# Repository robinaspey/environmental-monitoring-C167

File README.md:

# C167 environmental-monitoring source code
Legacy code for Siemens C167 microcontroller board which was for the EU Transport futures project. The Compiler used was KEIL Microvision 2. Assembler and Ansi C as well as binary files from the board OEM are included although the ASM and C driver and main program files were for the project. The additional hardware for the board was a custom photodetector board which had gain increments of x10, x100 and x1000 under control of the C167 dependent on the signal level

This code reads the ADC values for R,G,B channels from a photovolaic spectrometer which used the Mazet 3 channel photo diode with an OPA111 preamplifier from Burr Brown. The probe was used in the exhaust of a bus, and was also tested with various smoke sources
to allow detection of particulates and particulat bursts during vehicle operation.

This is legacy source code from 2001, so another of my old embedded projects

The files are all Ansi C and include:

1. Project main file: mtf0.c, mtf1.c, mtf2.c, mtf3.c, mtf4.c (revisions not under VCS)
2. Flash memory file system file (ff_flash.c)
3. Drivers for the main program  

Interfacing to the microcontroller is via a monitor program which is accessed by the serial
terminal and pressing <ESC> while the microcontroller reboots.

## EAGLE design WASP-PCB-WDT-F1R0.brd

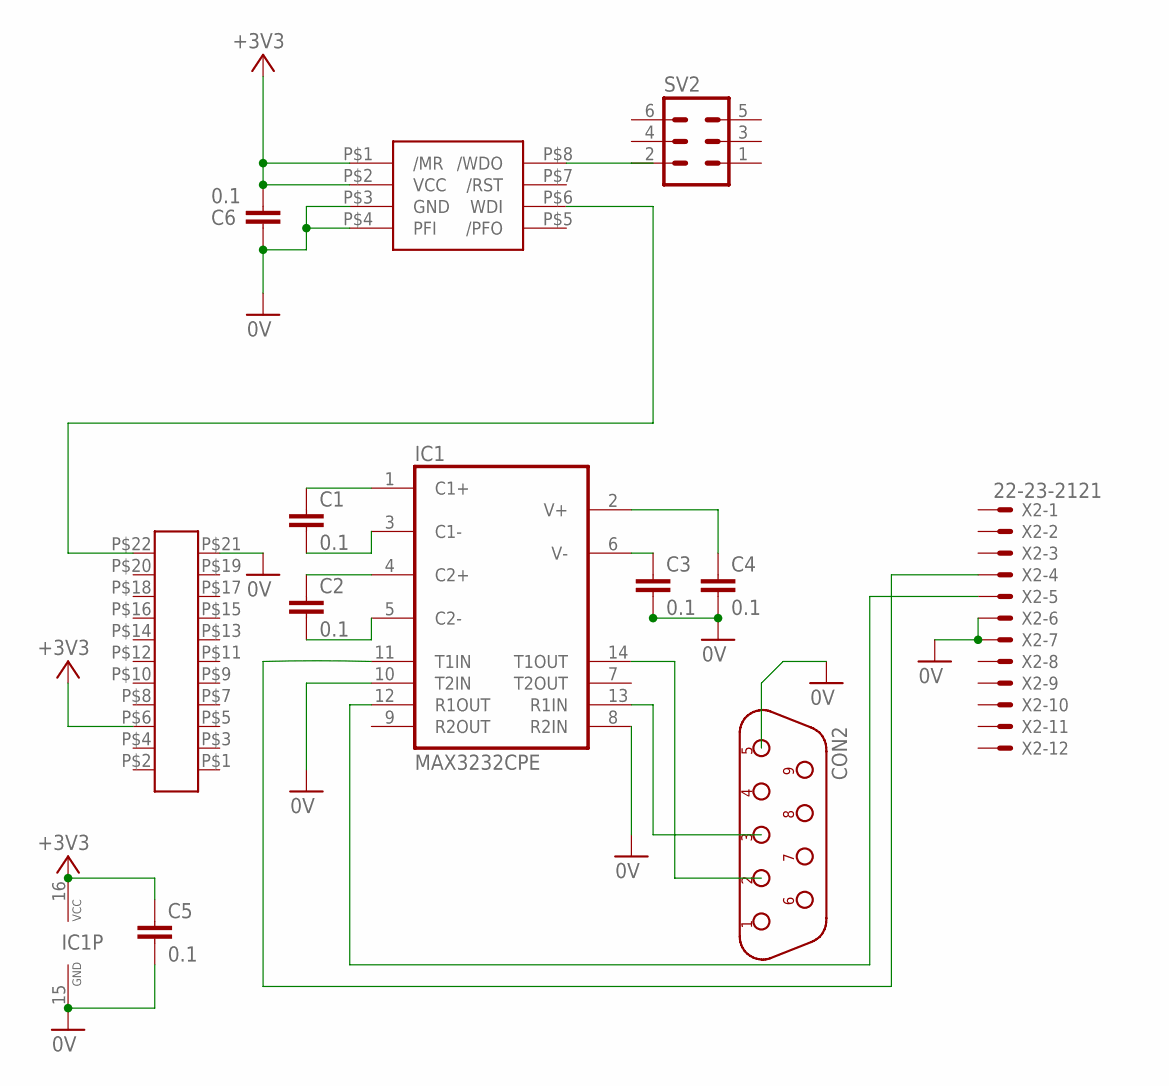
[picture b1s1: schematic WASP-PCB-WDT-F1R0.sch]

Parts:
C1, C2, C3, C4, C5, C6: 0.1; C5B2.5
CON2: CONNECT_DB9F/90; CONNECT_D-09F/90
IC1: MAX3232CPE; DIL16
SV2: CON-ML_ML6
U$2: ML22PML22P-PKG; CON-ML-22P
U$3: ADM706P
X2: 22-23-2121

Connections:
0V: C3.2, C4.2, C5.2, C6.2, CON2.5, IC1.8 (R2IN), IC1.10 (T2IN), IC1.15 (GND), U$2.P$21 (21), U$3.P$3 (GND), U$3.P$4 (PFI), X2.6, X2.7
14: U$2.P$14 (14)
+3V3: C5.1, C6.1, IC1.16 (VCC), U$2.P$6 (6), U$3.P$1 (/MR), U$3.P$2 (VCC)
unnamed: U$2.P$22 (22), U$3.P$6 (WDI)
unnamed: C1.1, IC1.1 (C1+)
unnamed: C1.2, IC1.3 (C1-)
unnamed: C2.1, IC1.4 (C2+)
unnamed: C2.2, IC1.5 (C2-)
unnamed: C4.1, IC1.2 (V+)
unnamed: C3.1, IC1.6 (V-)
unnamed: IC1.12 (R1OUT), X2.5
unnamed: SV2.2, U$3.P$8 (/WDO)
unnamed: CON2.3, IC1.13 (R1IN)
T1IN: IC1.11 (T1IN), X2.4
T1OUT: CON2.2, IC1.14 (T1OUT)

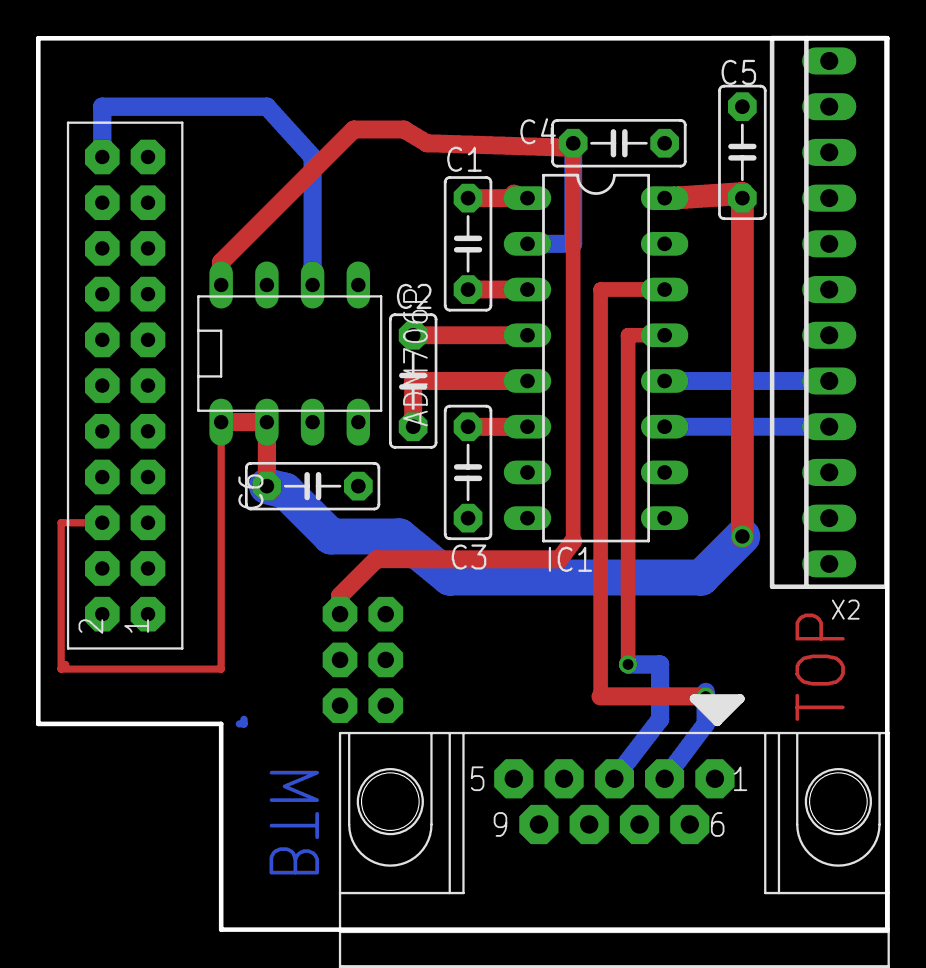
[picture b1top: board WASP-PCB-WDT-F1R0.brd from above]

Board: 2 copper layers, 47.2 x 49.5 mm, 12 parts (1 on the bottom side), 14 nets.

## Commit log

2017-12-09 Update README.md
    This commit by R.A.Aspey
2017-12-09 Files uploaded including source code c / asm files
2017-12-09 Update mpt0.c
    Aligned comments for viewing on github
2017-12-09 Update mtf.uv2
    Small revision to the comments at the top for github
2017-12-09 Update mtf1.c
    Refactor of code to align tab stops
2017-12-09 Update mtf2.c
    Refactor for github
2017-12-09 Update mtf3.c
    Refactor for github
2017-12-09 Update mtf4.c
    Refactor for github
2017-12-09 watchdog and serial interface board
    Cadsoft Eagle files
